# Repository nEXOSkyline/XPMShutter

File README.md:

ABSTRACT
  
   In this project, we tested the efficacy of a new control box developed to override PC signal and increase functionality of the XPM. 
   Due to the high shutter reaction speed causing slight displacements in laser direction, the data recorded from the experiment was at 
   risk of being less accurate. To improve these measurements, we developed a new control system to decrease any directional variation and 
   increase the accuracy of the data. Along with this, being able to override the computer signal provides a manual alternative to keep the 
   shutter in a fixed state when necessary. (See Fig. 1)
       
INTRO

   nEXO (next-generation Enriched Xenon Observatory) is a proposed experiment in pursuit of a rare type of radioactive decay in 136Xe called
   neutrinoless double-beta decay. Xenon being the element of observation, it is necessary to measure the chemical purity of the liquid xenon
   (LXe) used in the experiment, since the presence of impurities can degrade the signal from the detector. To detect these impurities, a Xenon
   Purity Monitor (XPM) was developed and installed at SLAC National Accelerator Laboratory. This experiment is used as a method to determine
   which materials are suitable to be placed in direct contact with LXe in the detector.
   
METHODS AND MATERIALS

  For the experimental setup, we used the override control box to be tested, an Arduino Ethernet Shield 2, an external solenoid to simulate the 
  shutter, a spring, and a 300mH inductor. First, we tested the control box that was built with a single inductor to slow the shutter reaction 
  speed. While this slowed the initial pull of the solenoid, we found that the force exerted by the spring was too strong for the inductor to 
  affect its release speed. In an attempt to fix this, we added a second inductor, which still had negligible effect on the release speed. 
  (See Experimental Results) In addition to physical testing, we developed software to monitor the current measured across the “shutter” over
  time, as well as implement the theoretical idea of modifying the duty cycle of the PC signal and test the effect that this would have on our 
  setup.
  
EXPERIMENTAL RESULTS

  The results of this experiment showed that using a 300mH inductor improved the reaction of the laser shutter when closing, but not when 
  opening, and that the control box can successfully override the computer signal.

THEORETICAL RESULTS

  (Fig. 2) The simulated inductor current vs duty cycle data. In order to counteract the linear force of the spring, we will moderate the
  duty cycle from the PC, forcing the current change into a linear form.
  
CONCLUSION

  In conclusion, we found that we were able to electrically override the PC signal with the control box. Our next step toward improving the 
  efficacy of the override control system is to control the current using the Arduino, forcing a pulsing pattern instead of the constant 
  current previously tested. In theory, this would mean that we are able to gradually lower the current rather than stopping it completely.
  (See Fig. 2)

WORKS CITED

  Aspects of the R&D for the Enriched Xenon Observatory for double beta decay
  by Wamba, Kolo, PhD Thesis, Stanford University, 2007
  A Xenon Gas Purity Monitor for EXO
  by Dobi, A., SLAC National Accelerator Laboratory, 2011

This material is based upon work supported by the U.S. Department of Energy, Office of Science, Office of Nuclear Structure & Nuclear 
Astrophysics, Pathways to Improved Representation in Nuclear Science under Award Number DE-SC0021954.

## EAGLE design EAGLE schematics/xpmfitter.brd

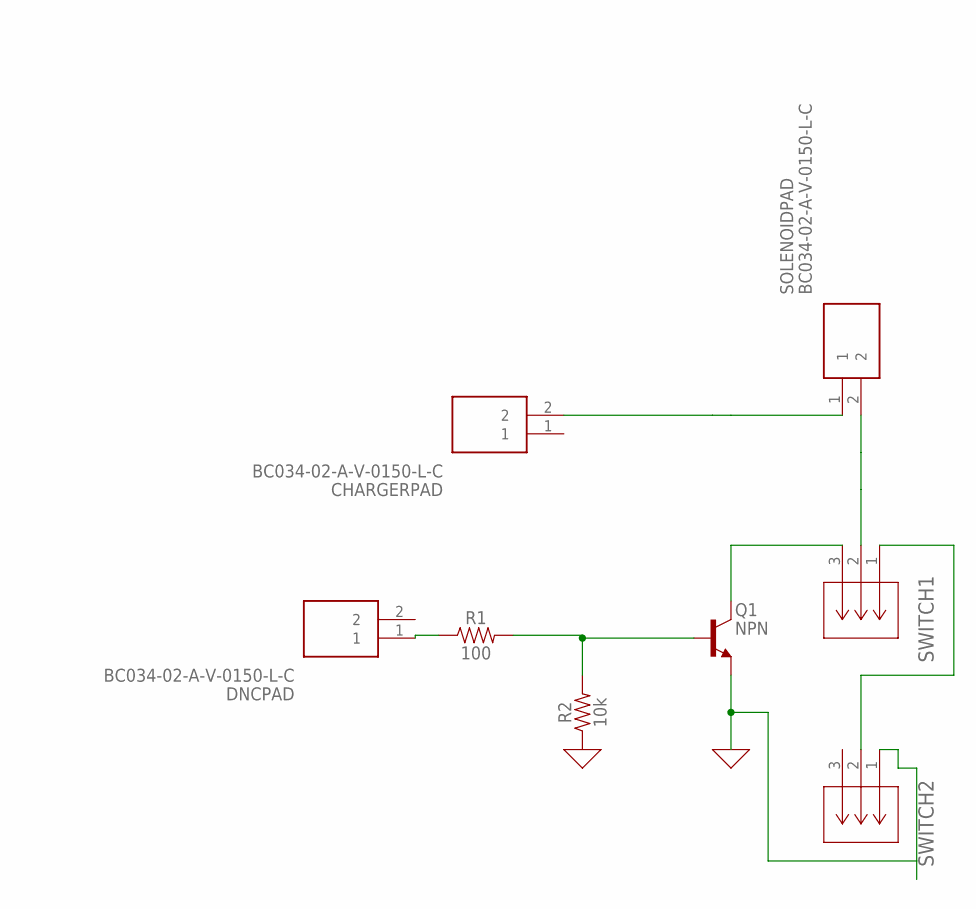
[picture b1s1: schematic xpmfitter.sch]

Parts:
CHARGERPAD: BC034-02-A-V-0150-L-C; BC03402AV0150LC
DNCPAD: BC034-02-A-V-0150-L-C; BC03402AV0150LC
Q1: NPN; SC59
R1: 100; 0603
R2: 10k; 0603
SOLENOIDPAD: BC034-02-A-V-0150-L-C; BC03402AV0150LC
SWITCH1, SWITCH2: GRPB031VWTC-RCCONN3_GRPB031_SUL; CONN3_GRPB031_SUL

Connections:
GND: Q1.E, R2.1, SWITCH2.1
unnamed: Q1.B, R1.2, R2.2
unnamed: Q1.C, SWITCH1.3
unnamed: CHARGERPAD.2, SOLENOIDPAD.1
unnamed: DNCPAD.1, R1.1
unnamed: SOLENOIDPAD.2, SWITCH1.2
unnamed: SWITCH1.1, SWITCH2.2

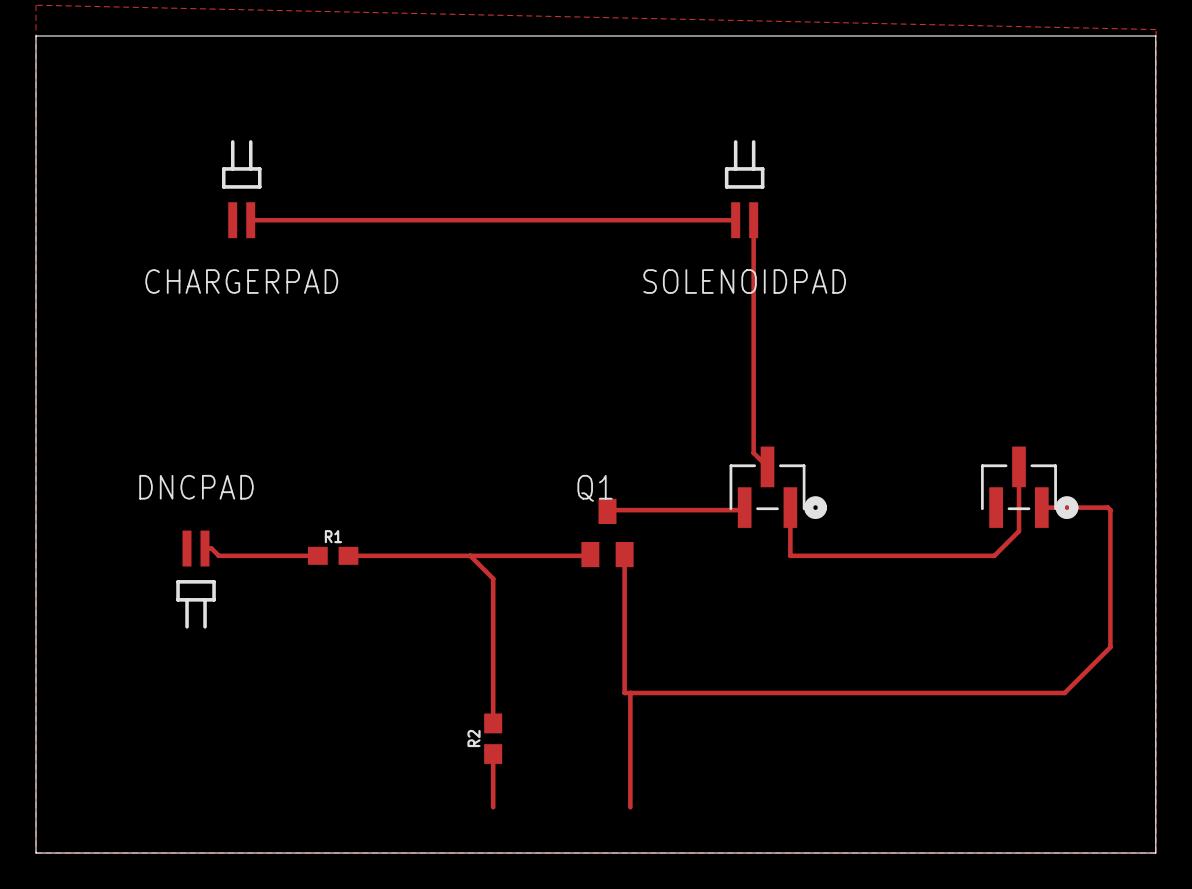
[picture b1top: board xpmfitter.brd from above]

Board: 2 copper layers, 62.2 x 45.4 mm, 8 parts (0 on the bottom side), 7 nets.

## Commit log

2022-07-12 latest files from old repo
2023-05-17 Add files via upload
    A GUI which allows the user to commit two values each for current pulses and pauses used to control the motion of a solenoid.
2023-05-23 Add files via upload
    With lines uncommented so it works
2023-07-11 Add files via upload
    files for printed board

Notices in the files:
parts and their libraries:
SparkFun-Resistors: Licensing: Creative Commons ShareAlike 4.0 International - https://creativecommons.org/licenses/by-sa/4.0
COPYRIGHT: Copyright (C) 2023 Ultra Librarian. All rights reserved.
